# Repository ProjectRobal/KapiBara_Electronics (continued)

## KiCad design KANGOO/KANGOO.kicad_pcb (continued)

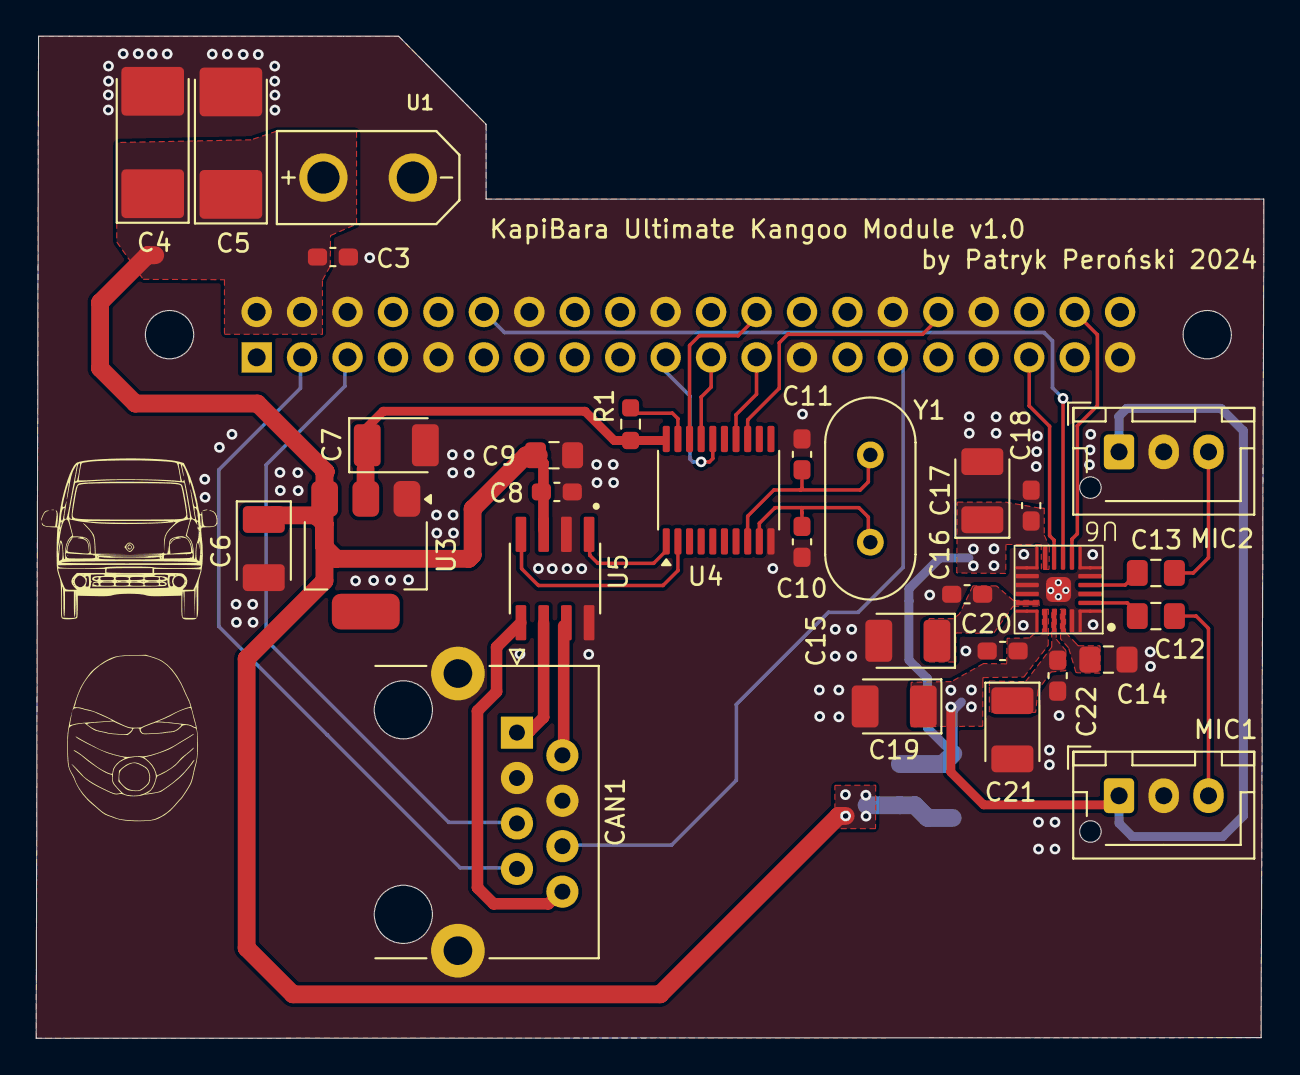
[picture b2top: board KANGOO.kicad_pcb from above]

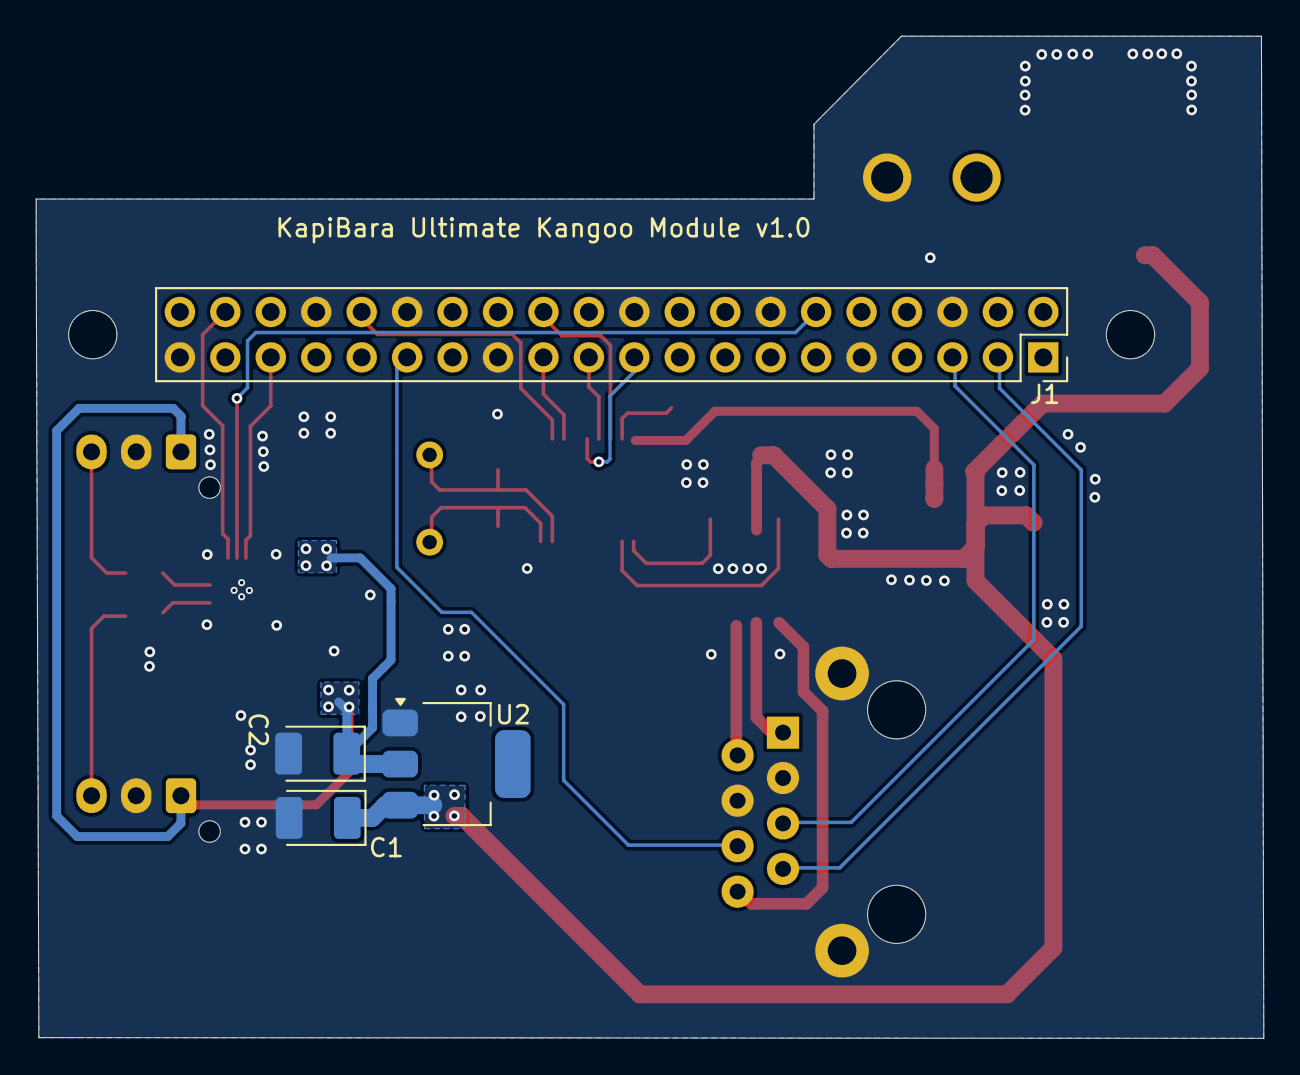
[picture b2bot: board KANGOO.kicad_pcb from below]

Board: 2 copper layers, 68.6 x 56.0 mm, 36 parts (4 on the bottom side), 31 nets.

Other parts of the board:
MH1, MH2: MountingHole_2.7mm_M2.5

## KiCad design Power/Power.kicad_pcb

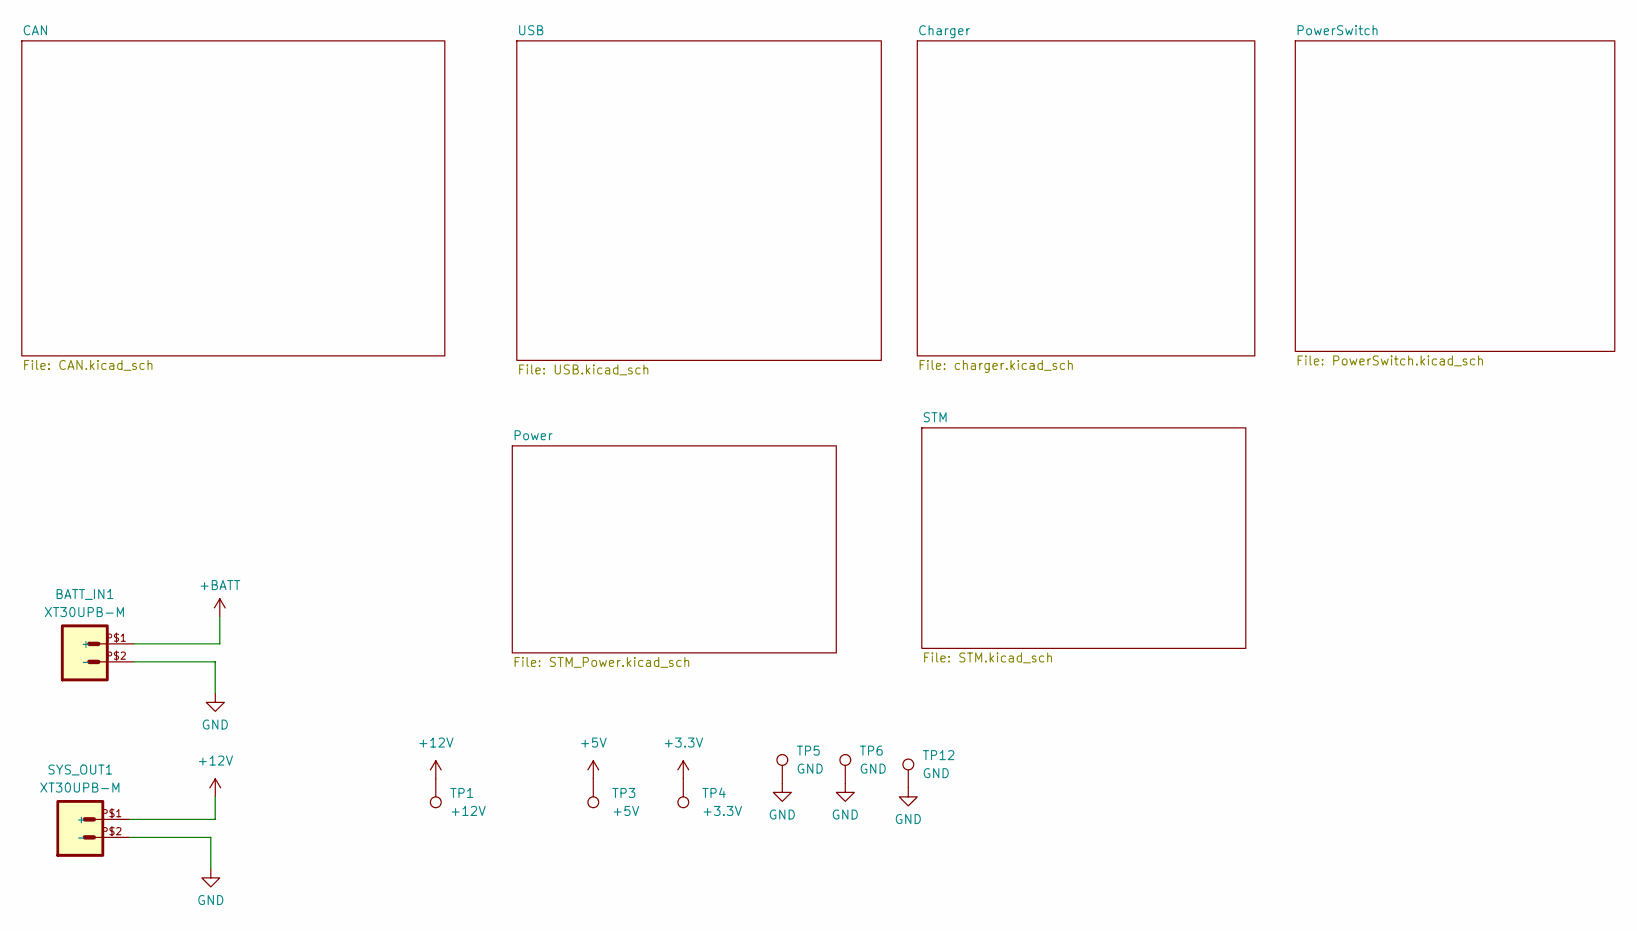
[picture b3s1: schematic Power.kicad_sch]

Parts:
BATT_IN1: XT30UPB-M
SYS_OUT1: XT30UPB-M
TP1: +12V; TestPoint_Pad_1.0x1.0mm
TP3: +5V; TestPoint_Pad_1.0x1.0mm
TP4: +3.3V; TestPoint_Pad_1.0x1.0mm
TP5, TP6, TP12: GND; TestPoint_Pad_1.0x1.0mm

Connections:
+3.3V: TP4.1; also elsewhere on the board
+5V: TP3.1; also elsewhere on the board
+12V: SYS_OUT1.P$1 (+), TP1.1; also elsewhere on the board
+BATT: BATT_IN1.P$1 (+); also elsewhere on the board
GND: BATT_IN1.P$2 (-), SYS_OUT1.P$2 (-), TP5.1, TP6.1, TP12.1; also elsewhere on the board

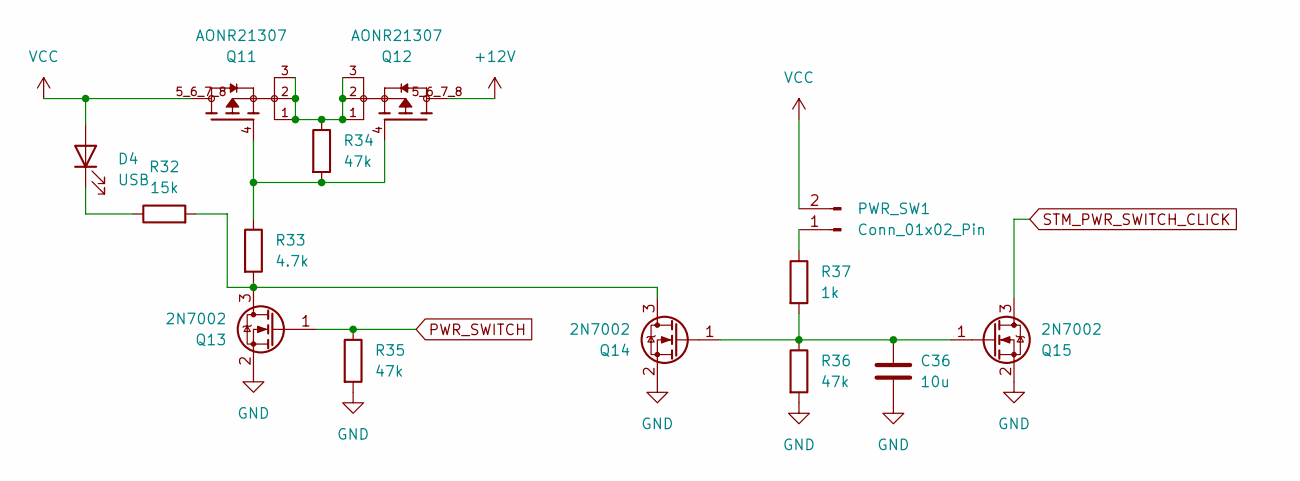
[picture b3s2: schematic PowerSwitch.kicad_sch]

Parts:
C36: 10u; C_0603_1608Metric_Pad1.08x0.95mm_HandSolder
D4: USB; LED_0603_1608Metric_Pad1.05x0.95mm_HandSolder
PWR_SW1: Conn_01x02_Pin; JST_XH_B2B-XH-A_1x02_P2.50mm_Vertical
Q11, Q12: AONR21307; TRANS_AONR21307; PARTREV 1.1
Q13, Q14, Q15: 2N7002; SOT-23
R32: 15k; R_0603_1608Metric_Pad0.98x0.95mm_HandSolder
R33: 4.7k; R_0603_1608Metric_Pad0.98x0.95mm_HandSolder
R34, R35, R36: 47k; R_0603_1608Metric_Pad0.98x0.95mm_HandSolder
R37: 1k; R_0603_1608Metric_Pad0.98x0.95mm_HandSolder

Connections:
+12V: Q12.5_6_7_8; also elsewhere on the board
GND: C36.2, Q13.2 (S), Q14.2 (S), Q15.2 (S), R35.2, R36.2; also elsewhere on the board
unnamed: D4.1 (K), R32.1
unnamed: PWR_SW1.1, R37.1
unnamed: Q11.1, Q11.2, Q11.3, Q12.1, Q12.2, Q12.3, R34.1
unnamed: Q11.4, Q12.4, R33.1, R34.2
unnamed: Q13.3 (D), Q14.3 (D), R32.2, R33.2
unnamed: C36.1, Q14.1 (G), Q15.1 (G), R36.1, R37.2
PWR_SWITCH: Q13.1 (G), R35.1; also elsewhere on the board
STM_PWR_SWITCH_CLICK: Q15.3 (D); also elsewhere on the board
VCC: D4.2 (A), PWR_SW1.2, Q11.5_6_7_8; also elsewhere on the board

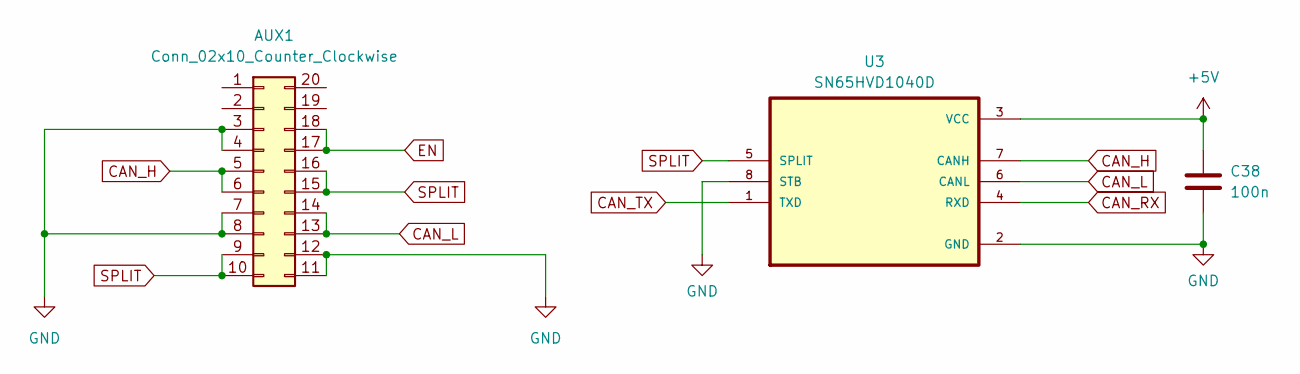
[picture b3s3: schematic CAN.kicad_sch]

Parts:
AUX1: Conn_02x10_Counter_Clockwise; IDC-Header_2x10_P2.54mm_Vertical
C38: 100n; C_0603_1608Metric_Pad1.08x0.95mm_HandSolder
U3: SN65HVD1040D; SOIC127P599X175-8N

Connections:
+5V: C38.1, U3.3 (VCC); also elsewhere on the board
CAN_H: AUX1.5, AUX1.6, U3.7 (CANH)
CAN_L: AUX1.13, AUX1.14, U3.6 (CANL)
CAN_RX: U3.4 (RXD); also elsewhere on the board
CAN_TX: U3.1 (TXD); also elsewhere on the board
EN: AUX1.17, AUX1.18; also elsewhere on the board
GND: AUX1.3, AUX1.4, AUX1.7, AUX1.8, AUX1.11, AUX1.12, C38.2, U3.2 (GND), U3.8 (STB); also elsewhere on the board
SPLIT: AUX1.9, AUX1.10, AUX1.15, AUX1.16, U3.5 (SPLIT)

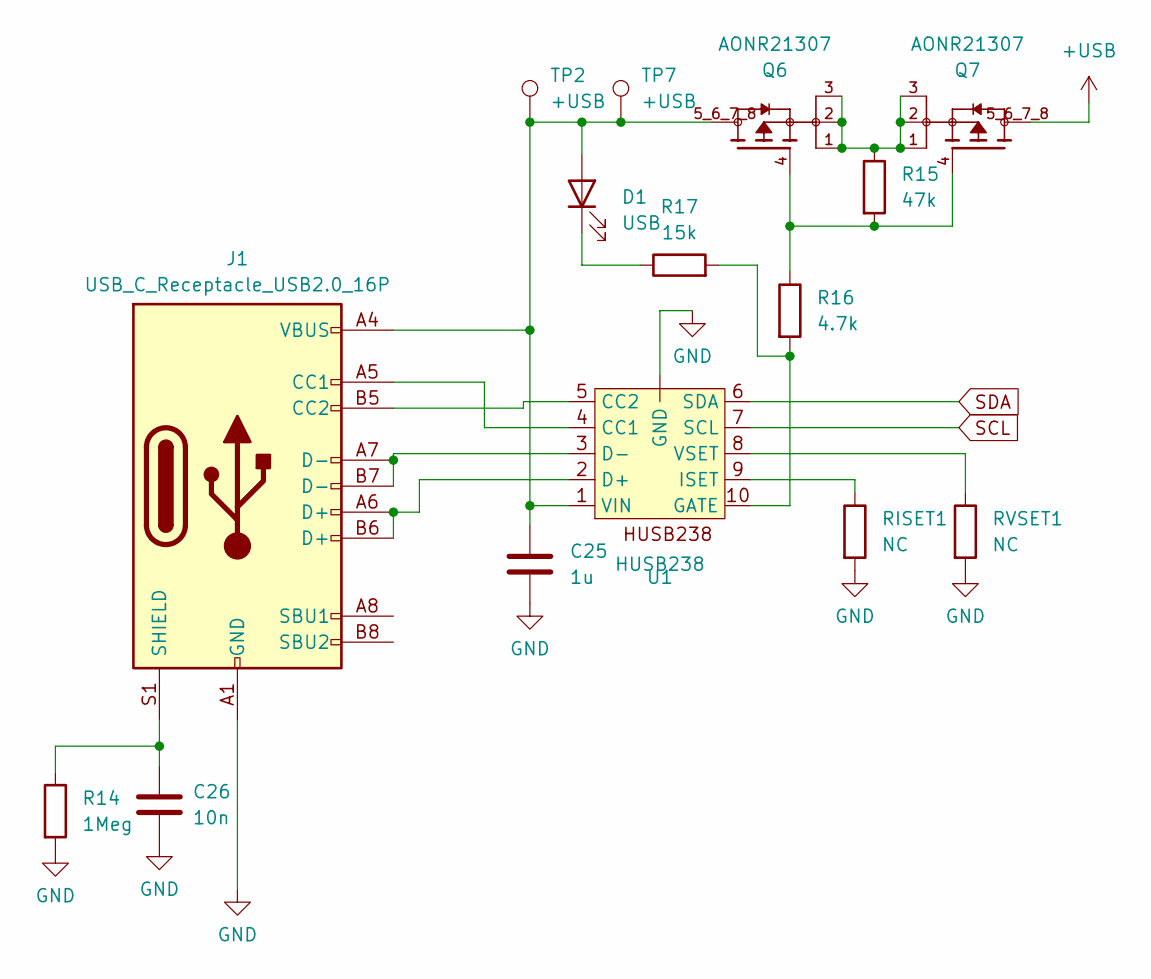
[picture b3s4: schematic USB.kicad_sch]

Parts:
C25: 1u; C_0805_2012Metric_Pad1.18x1.45mm_HandSolder
C26: 10n; C_0805_2012Metric_Pad1.18x1.45mm_HandSolder
D1: USB; LED_0603_1608Metric_Pad1.05x0.95mm_HandSolder
J1: USB_C_Receptacle_USB2.0_16P; USB_C_Receptacle_HRO_TYPE-C-31-M-12
Q6, Q7: AONR21307; TRANS_AONR21307; PARTREV 1.1
R14: 1Meg; R_0805_2012Metric_Pad1.20x1.40mm_HandSolder
R15: 47k; R_0603_1608Metric_Pad0.98x0.95mm_HandSolder
R16: 4.7k; R_0603_1608Metric_Pad0.98x0.95mm_HandSolder
R17: 15k; R_0603_1608Metric_Pad0.98x0.95mm_HandSolder
RISET1: NC; R_0603_1608Metric_Pad0.98x0.95mm_HandSolder
RVSET1: NC; R_0603_1608Metric_Pad0.98x0.95mm_HandSolder
TP2, TP7: +USB; TestPoint_Pad_1.0x1.0mm
U1: HUSB238; DFN-10-1EP_2.6x2.6mm_P0.5mm_EP1.3x2.2mm_ThermalVias

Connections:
+USB: Q7.5_6_7_8; also elsewhere on the board
GND: C25.2, C26.2, J1.A1 (GND), J1.A12 (GND), J1.B1 (GND), J1.B12 (GND), R14.2, RISET1.2, RVSET1.2, U1. (GND), U1.11; also elsewhere on the board
unnamed: C25.1, D1.2 (A), J1.A4 (VBUS), J1.A9 (VBUS), J1.B4 (VBUS), J1.B9 (VBUS), Q6.5_6_7_8, TP2.1, TP7.1, U1.1 (VIN)
unnamed: D1.1 (K), R17.1
unnamed: J1.A5 (CC1), U1.4 (CC1)
unnamed: J1.B5 (CC2), U1.5 (CC2)
unnamed: C26.1, J1.S1 (SHIELD), R14.1
unnamed: Q6.1, Q6.2, Q6.3, Q7.1, Q7.2, Q7.3, R15.1
unnamed: Q6.4, Q7.4, R15.2, R16.1
unnamed: J1.A6 (D+), J1.B6 (D+), U1.2 (D+)
unnamed: J1.A7 (D-), J1.B7 (D-), U1.3 (D-)
unnamed: R16.2, R17.2, U1.10 (GATE)
unnamed: RISET1.1, U1.9 (ISET)
unnamed: RVSET1.1, U1.8 (VSET)
SCL: U1.7 (SCL); also elsewhere on the board
SDA: U1.6 (SDA); also elsewhere on the board

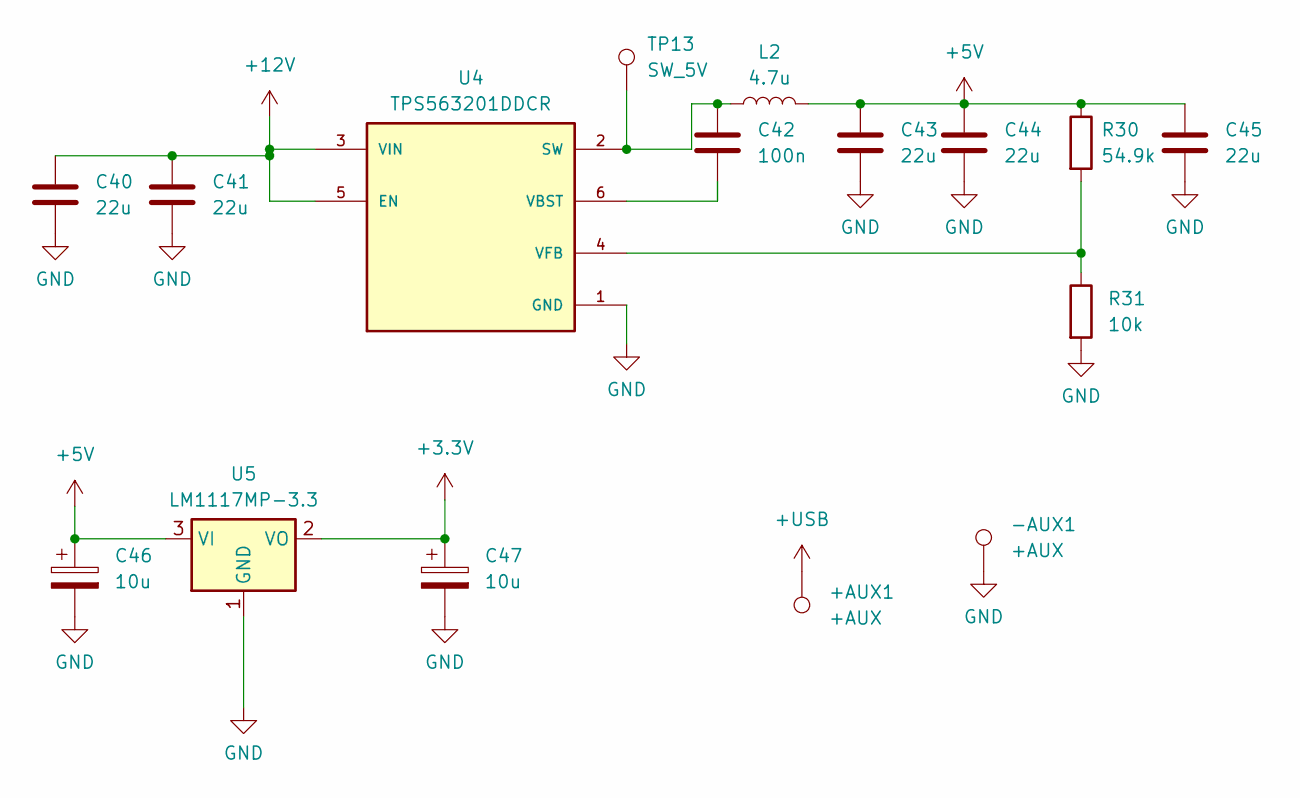
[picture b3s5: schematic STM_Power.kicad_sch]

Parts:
+AUX1: +AUX; TestPoint_Pad_2.5x2.5mm
-AUX1: +AUX; TestPoint_Pad_2.5x2.5mm
C40, C41, C43, C44, C45: 22u; C_0805_2012Metric_Pad1.18x1.45mm_HandSolder
C42: 100n; C_0603_1608Metric_Pad1.08x0.95mm_HandSolder
C46, C47: 10u; CP_EIA-3528-21_Kemet-B_Pad1.50x2.35mm_HandSolder
L2: 4.7u; L_Changjiang_FNR6045S
R30: 54.9k; R_0603_1608Metric_Pad0.98x0.95mm_HandSolder
R31: 10k; R_0603_1608Metric_Pad0.98x0.95mm_HandSolder
TP13: SW_5V; TestPoint_Pad_1.0x1.0mm
U4: TPS563201DDCR; SOT95P280X110-6N; PARTREV December 2015
U5: LM1117MP-3.3; SOT-223

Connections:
+3.3V: C47.1, U5.2 (VO); also elsewhere on the board
+5V: C43.1, C44.1, C45.1, C46.1, L2.2, R30.1, U5.3 (VI); also elsewhere on the board
+12V: C40.1, C41.1, U4.3 (VIN), U4.5 (EN); also elsewhere on the board
+USB: +AUX1.1; also elsewhere on the board
GND: -AUX1.1, C40.2, C41.2, C43.2, C44.2, C45.2, C46.2, C47.2, R31.2, U4.1 (GND), U5.1 (GND); also elsewhere on the board
unnamed: C42.2, L2.1, TP13.1, U4.2 (SW)
unnamed: C42.1, U4.6 (VBST)
unnamed: R30.2, R31.1, U4.4 (VFB)

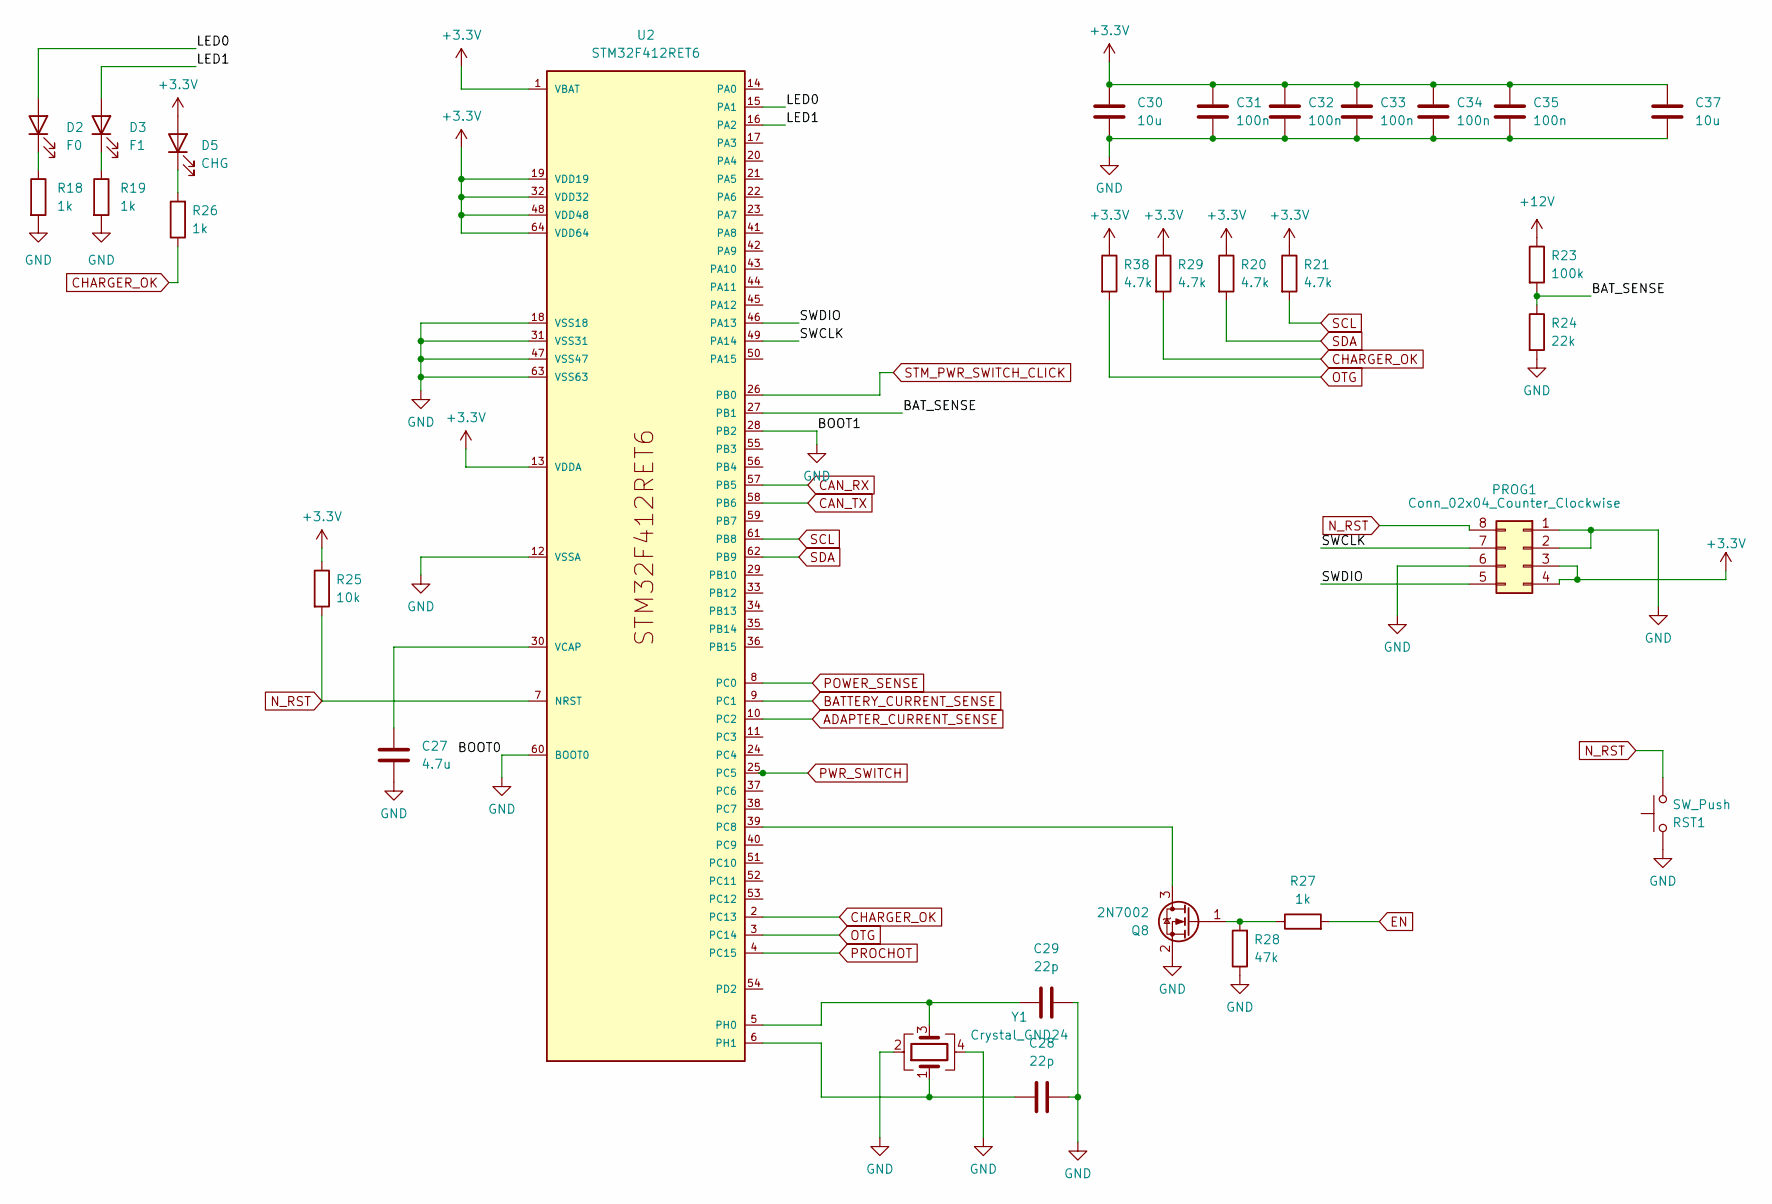
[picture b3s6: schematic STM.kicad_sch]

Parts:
C27: 4.7u; C_0805_2012Metric_Pad1.18x1.45mm_HandSolder
C28, C29: 22p; C_0603_1608Metric_Pad1.08x0.95mm_HandSolder
C30, C37: 10u; C_0805_2012Metric_Pad1.18x1.45mm_HandSolder
C31, C32, C33, C34, C35: 100n; C_0603_1608Metric_Pad1.08x0.95mm_HandSolder
D2: F0; LED_0603_1608Metric_Pad1.05x0.95mm_HandSolder
D3: F1; LED_0603_1608Metric_Pad1.05x0.95mm_HandSolder
D5: CHG; LED_0603_1608Metric_Pad1.05x0.95mm_HandSolder
PROG1: Conn_02x04_Counter_Clockwise; PinHeader_2x04_P2.54mm_Vertical
Q8: 2N7002; SOT-23
R18, R19, R26, R27: 1k; R_0603_1608Metric_Pad0.98x0.95mm_HandSolder
R20, R21, R29, R38: 4.7k; R_0603_1608Metric_Pad0.98x0.95mm_HandSolder
R23: 100k; R_0603_1608Metric_Pad0.98x0.95mm_HandSolder
R24: 22k; R_0603_1608Metric_Pad0.98x0.95mm_HandSolder
R25: 10k; R_0603_1608Metric_Pad0.98x0.95mm_HandSolder
R28: 47k; R_0603_1608Metric_Pad0.98x0.95mm_HandSolder
RST1: SW_Push; SW_SPST_PTS647_Sx50
U2: STM32F412RET6; LQFP-10X10-64
Y1: Crystal_GND24; Crystal_SMD_2520-4Pin_2.5x2.0mm

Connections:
+3.3V: C30.1, C31.1, C32.1, C33.1, C34.1, C35.1, C37.1, D5.2 (A), PROG1.3, PROG1.4, R20.1, R21.1, R25.1, R29.1, R38.1, U2.1 (VBAT), U2.13 (VDDA), U2.19 (VDD19), U2.32 (VDD32), U2.48 (VDD48), U2.64 (VDD64); also elsewhere on the board
+12V: R23.1; also elsewhere on the board
/STM/BAT_SENSE: R23.2, R24.1, U2.27 (PB1)
/STM/LED0: D2.2 (A), U2.15 (PA1)
/STM/LED1: D3.2 (A), U2.16 (PA2)
/STM/SWCLK: PROG1.7, U2.49 (PA14)
/STM/SWDIO: PROG1.5, U2.46 (PA13)
ADAPTER_CURRENT_SENSE: U2.10 (PC2); also elsewhere on the board
BATTERY_CURRENT_SENSE: U2.9 (PC1); also elsewhere on the board
CAN_RX: U2.57 (PB5); also elsewhere on the board
CAN_TX: U2.58 (PB6); also elsewhere on the board
CHARGER_OK: R26.1, R29.2, U2.2 (PC13); also elsewhere on the board
EN: R27.2; also elsewhere on the board
GND: C27.2, C28.2, C29.2, C30.2, C31.2, C32.2, C33.2, C34.2, C35.2, C37.2, PROG1.1, PROG1.2, PROG1.6, Q8.2 (S), R18.2, R19.2, R24.2, R28.1, RST1.2, U2.12 (VSSA), U2.18 (VSS18), U2.28 (PB2), U2.31 (VSS31), U2.47 (VSS47), U2.60 (BOOT0), U2.63 (VSS63), Y1.2, Y1.4; also elsewhere on the board
N_RST: PROG1.8, R25.2, RST1.1, U2.7 (NRST)
unnamed: D2.1 (K), R18.1
unnamed: D3.1 (K), R19.1
unnamed: D5.1 (K), R26.2
unnamed: Q8.3 (D), U2.39 (PC8)
unnamed: Q8.1 (G), R27.1, R28.2
unnamed: C29.1, U2.5 (PH0), Y1.3
unnamed: C28.1, U2.6 (PH1), Y1.1
unnamed: C27.1, U2.30 (VCAP)
OTG: R38.2, U2.3 (PC14); also elsewhere on the board
POWER_SENSE: U2.8 (PC0); also elsewhere on the board
PROCHOT: U2.4 (PC15); also elsewhere on the board
PWR_SWITCH: U2.25 (PC5); also elsewhere on the board
SCL: R21.2, U2.61 (PB8); also elsewhere on the board
SDA: R20.2, U2.62 (PB9); also elsewhere on the board
STM_PWR_SWITCH_CLICK: U2.26 (PB0); also elsewhere on the board

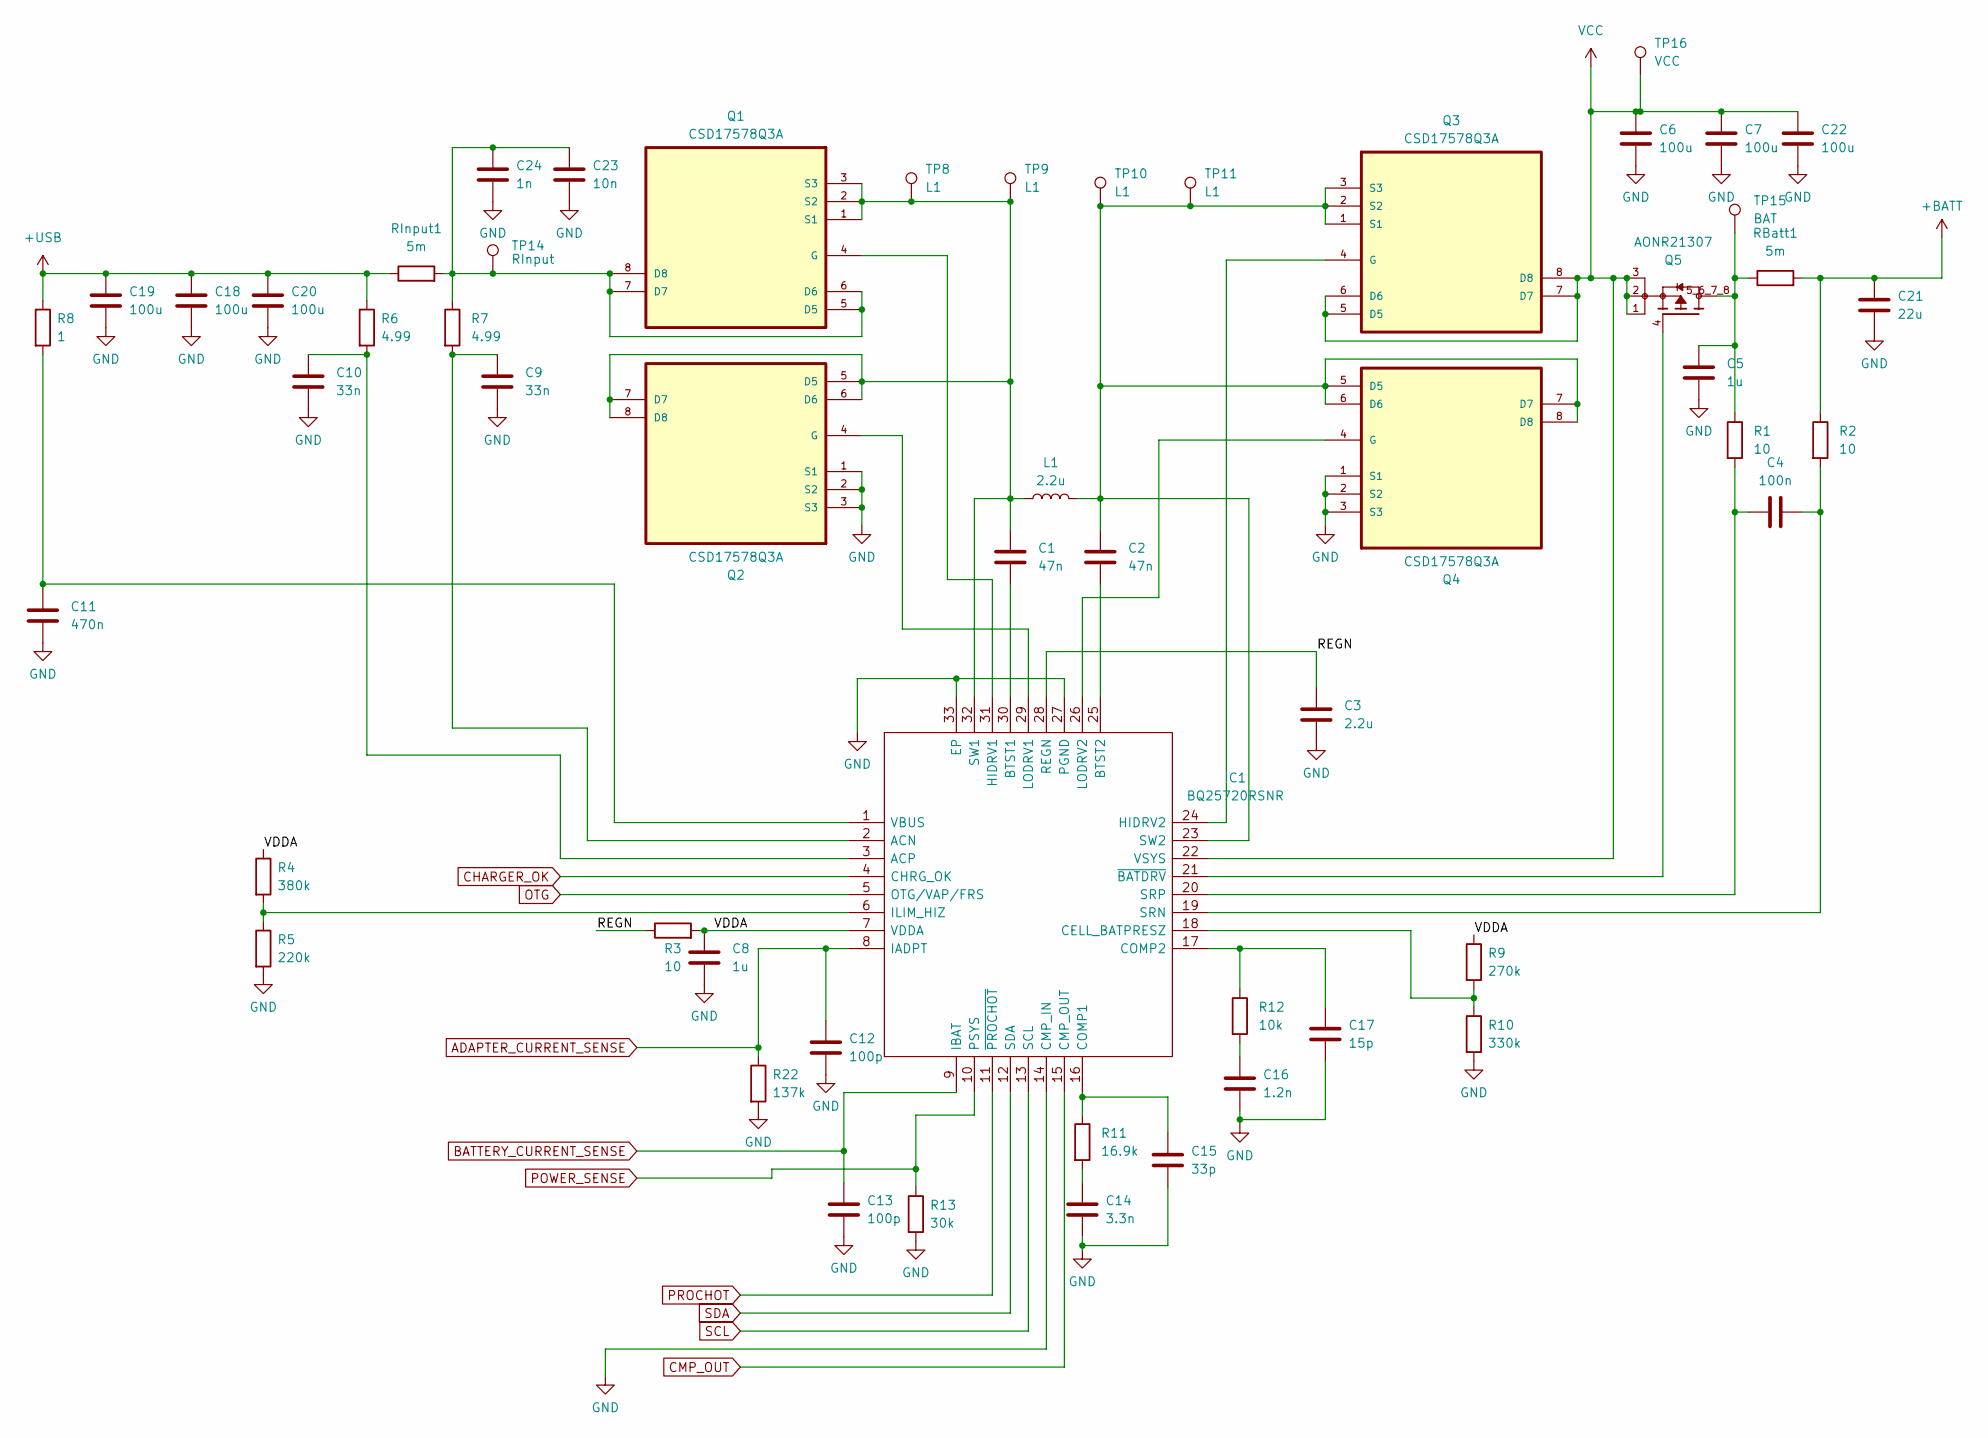
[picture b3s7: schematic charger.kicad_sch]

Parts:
C1, C2: 47n; C_0805_2012Metric_Pad1.18x1.45mm_HandSolder
C3: 2.2u; C_0805_2012Metric_Pad1.18x1.45mm_HandSolder
C4: 100n; C_0603_1608Metric_Pad1.08x0.95mm_HandSolder
C5, C8: 1u; C_0805_2012Metric_Pad1.18x1.45mm_HandSolder
C6, C7, C18, C19, C20, C22: 100u; C_1206_3216Metric_Pad1.33x1.80mm_HandSolder
C9, C10: 33n; C_0603_1608Metric_Pad1.08x0.95mm_HandSolder
C11: 470n; C_0603_1608Metric_Pad1.08x0.95mm_HandSolder
C12, C13: 100p; C_0603_1608Metric_Pad1.08x0.95mm_HandSolder
C14: 3.3n; C_0805_2012Metric_Pad1.18x1.45mm_HandSolder
C15: 33p; C_0805_2012Metric_Pad1.18x1.45mm_HandSolder
C16: 1.2n; C_0603_1608Metric_Pad1.08x0.95mm_HandSolder
C17: 15p; C_0603_1608Metric_Pad1.08x0.95mm_HandSolder
C21: 22u; C_1206_3216Metric_Pad1.33x1.80mm_HandSolder
C23: 10n; C_0603_1608Metric_Pad1.08x0.95mm_HandSolder
C24: 1n; C_0603_1608Metric_Pad1.08x0.95mm_HandSolder
IC1: BQ25720RSNR; QFN40P400X400X80-33N-D; Mouser Part Number 595-BQ25720RSNR
L1: 2.2u; L_TaiTech_TMPC1265_13.5x12.5mm
Q1, Q2, Q3, Q4: CSD17578Q3A; TRANS_CSD18543Q3A
Q5: AONR21307; TRANS_AONR21307; PARTREV 1.1
R1, R2: 10; R_0603_1608Metric_Pad0.98x0.95mm_HandSolder
R3: 10; R_1206_3216Metric_Pad1.30x1.75mm_HandSolder
R4: 380k; R_0603_1608Metric_Pad0.98x0.95mm_HandSolder
R5: 220k; R_0603_1608Metric_Pad0.98x0.95mm_HandSolder
R6, R7: 4.99; R_0603_1608Metric_Pad0.98x0.95mm_HandSolder
R8: 1; R_0603_1608Metric_Pad0.98x0.95mm_HandSolder
R9: 270k; R_0603_1608Metric_Pad0.98x0.95mm_HandSolder
R10: 330k; R_0603_1608Metric_Pad0.98x0.95mm_HandSolder
R11: 16.9k; R_0603_1608Metric_Pad0.98x0.95mm_HandSolder
R12: 10k; R_0603_1608Metric_Pad0.98x0.95mm_HandSolder
R13: 30k; R_0603_1608Metric_Pad0.98x0.95mm_HandSolder
R22: 137k; R_0603_1608Metric_Pad0.98x0.95mm_HandSolder
RBatt1: 5m; R_2010_5025Metric_Pad1.40x2.65mm_HandSolder
RInput1: 5m; R_2010_5025Metric_Pad1.40x2.65mm_HandSolder
TP8, TP9, TP10, TP11: L1; TestPoint_Pad_1.0x1.0mm
TP14: RInput; TestPoint_Pad_1.0x1.0mm
TP15: BAT; TestPoint_Pad_1.0x1.0mm
TP16: VCC; TestPoint_Pad_1.0x1.0mm

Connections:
+BATT: C21.1, R2.1, RBatt1.2; also elsewhere on the board
+USB: C18.1, C19.1, C20.1, R6.1, R8.1, RInput1.1; also elsewhere on the board
/Charger/REGN: C3.1, IC1.28 (REGN), R3.1
/Charger/VDDA: C8.1, IC1.7 (VDDA), R3.2, R4.1, R9.1
ADAPTER_CURRENT_SENSE: C12.1, IC1.8 (IADPT), R22.1; also elsewhere on the board
BATTERY_CURRENT_SENSE: C13.1, IC1.9 (IBAT); also elsewhere on the board
CHARGER_OK: IC1.4 (CHRG_OK); also elsewhere on the board
CMP_OUT: IC1.15 (CMP_OUT)
GND: C3.2, C5.2, C6.2, C7.2, C8.2, C9.2, C10.2, C11.2, C12.2, C13.2, C14.2, C15.2, C16.2, C17.2, C18.2, C19.2, C20.2, C21.2, C22.2, C23.2, C24.2, IC1.14 (CMP_IN), IC1.27 (PGND), IC1.33 (EP), Q2.1 (S1), Q2.2 (S2), Q2.3 (S3), Q4.1 (S1), Q4.2 (S2), Q4.3 (S3), R5.2, R10.2, R13.2, R22.2; also elsewhere on the board
NET-(IC1-SW): Q2.11
unnamed: C5.1, Q5.5_6_7_8, R1.1, RBatt1.1, TP15.1
unnamed: C14.1, R11.2
unnamed: C16.1, R12.2
unnamed: C9.1, IC1.2 (ACN), R7.2
unnamed: C10.1, IC1.3 (ACP), R6.2
unnamed: C1.2, IC1.30 (BTST1)
unnamed: C2.2, IC1.25 (BTST2)
unnamed: IC1.18 (CELL_BATPRESZ), R9.2, R10.1
unnamed: C15.1, IC1.16 (COMP1), R11.1
unnamed: C17.1, IC1.17 (COMP2), R12.1
unnamed: IC1.31 (HIDRV1), Q1.4 (G)
unnamed: IC1.24 (HIDRV2), Q3.4 (G)
unnamed: IC1.6 (ILIM_HIZ), R4.2, R5.1
unnamed: IC1.29 (LODRV1), Q2.4 (G)
unnamed: IC1.26 (LODRV2), Q4.4 (G)
unnamed: C4.1, IC1.19 (SRN), R2.2
unnamed: C4.2, IC1.20 (SRP), R1.2
unnamed: C1.1, IC1.32 (SW1), L1.1, Q1.1 (S1), Q1.2 (S2), Q1.3 (S3), Q2.5 (D5), Q2.6 (D6), Q2.7 (D7), Q2.8 (D8), Q2.9, Q2.10, Q2.12, TP8.1, TP9.1
unnamed: C2.1, IC1.23 (SW2), L1.2, Q3.1 (S1), Q3.2 (S2), Q3.3 (S3), Q4.5 (D5), Q4.6 (D6), Q4.7 (D7), Q4.8 (D8), Q4.9, Q4.10, Q4.11, Q4.12, TP10.1, TP11.1
unnamed: C11.1, IC1.1 (VBUS), R8.2
unnamed: IC1.21 (~BATDRV), Q5.4
unnamed: C23.1, C24.1, Q1.5 (D5), Q1.6 (D6), Q1.7 (D7), Q1.8 (D8), Q1.9, Q1.10, Q1.11, Q1.12, R7.1, RInput1.2, TP14.1
OTG: IC1.5 (OTG/VAP/FRS); also elsewhere on the board
POWER_SENSE: IC1.10 (PSYS), R13.1; also elsewhere on the board
PROCHOT: IC1.11 (~PROCHOT); also elsewhere on the board
SCL: IC1.13 (SCL); also elsewhere on the board
SDA: IC1.12 (SDA); also elsewhere on the board
VCC: C6.1, C7.1, C22.1, IC1.22 (VSYS), Q3.5 (D5), Q3.6 (D6), Q3.7 (D7), Q3.8 (D8), Q3.9, Q3.10, Q3.11, Q3.12, Q5.1, Q5.2, Q5.3, TP16.1; also elsewhere on the board

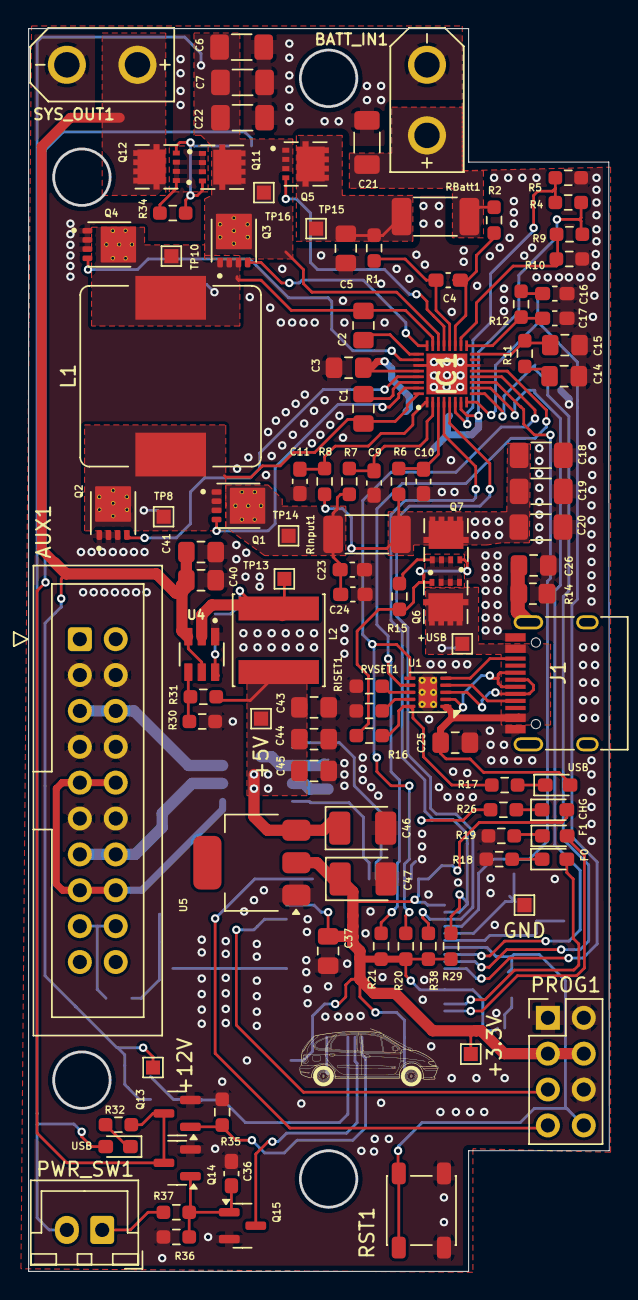
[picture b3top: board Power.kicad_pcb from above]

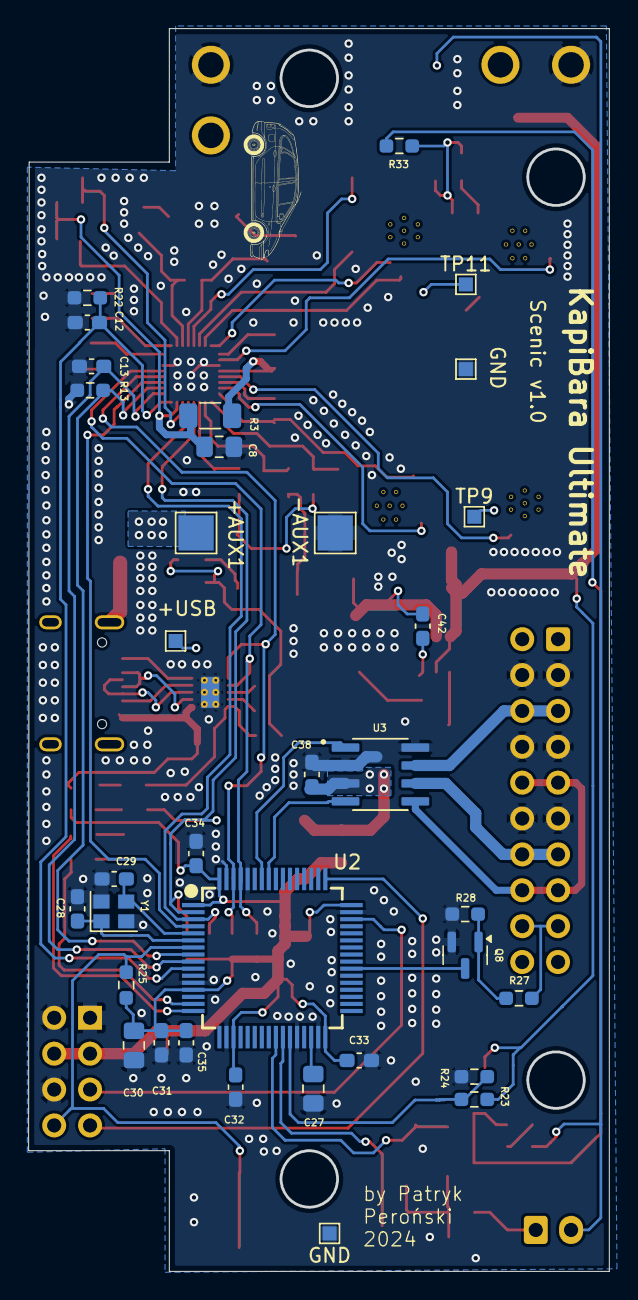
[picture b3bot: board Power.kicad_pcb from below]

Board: 2 copper layers, 41.1 x 88.0 mm, 140 parts (34 on the bottom side), 82 nets.
